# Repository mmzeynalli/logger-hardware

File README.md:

# logger-hardware
This is hardware design for Logger project, built in KiCAD. This project have three UARTs to log any three devices real-time with several options: logging to SD, sending to server (with SIM800), sending data over Bluetooth (to check it from mobile app) and OLED screen.

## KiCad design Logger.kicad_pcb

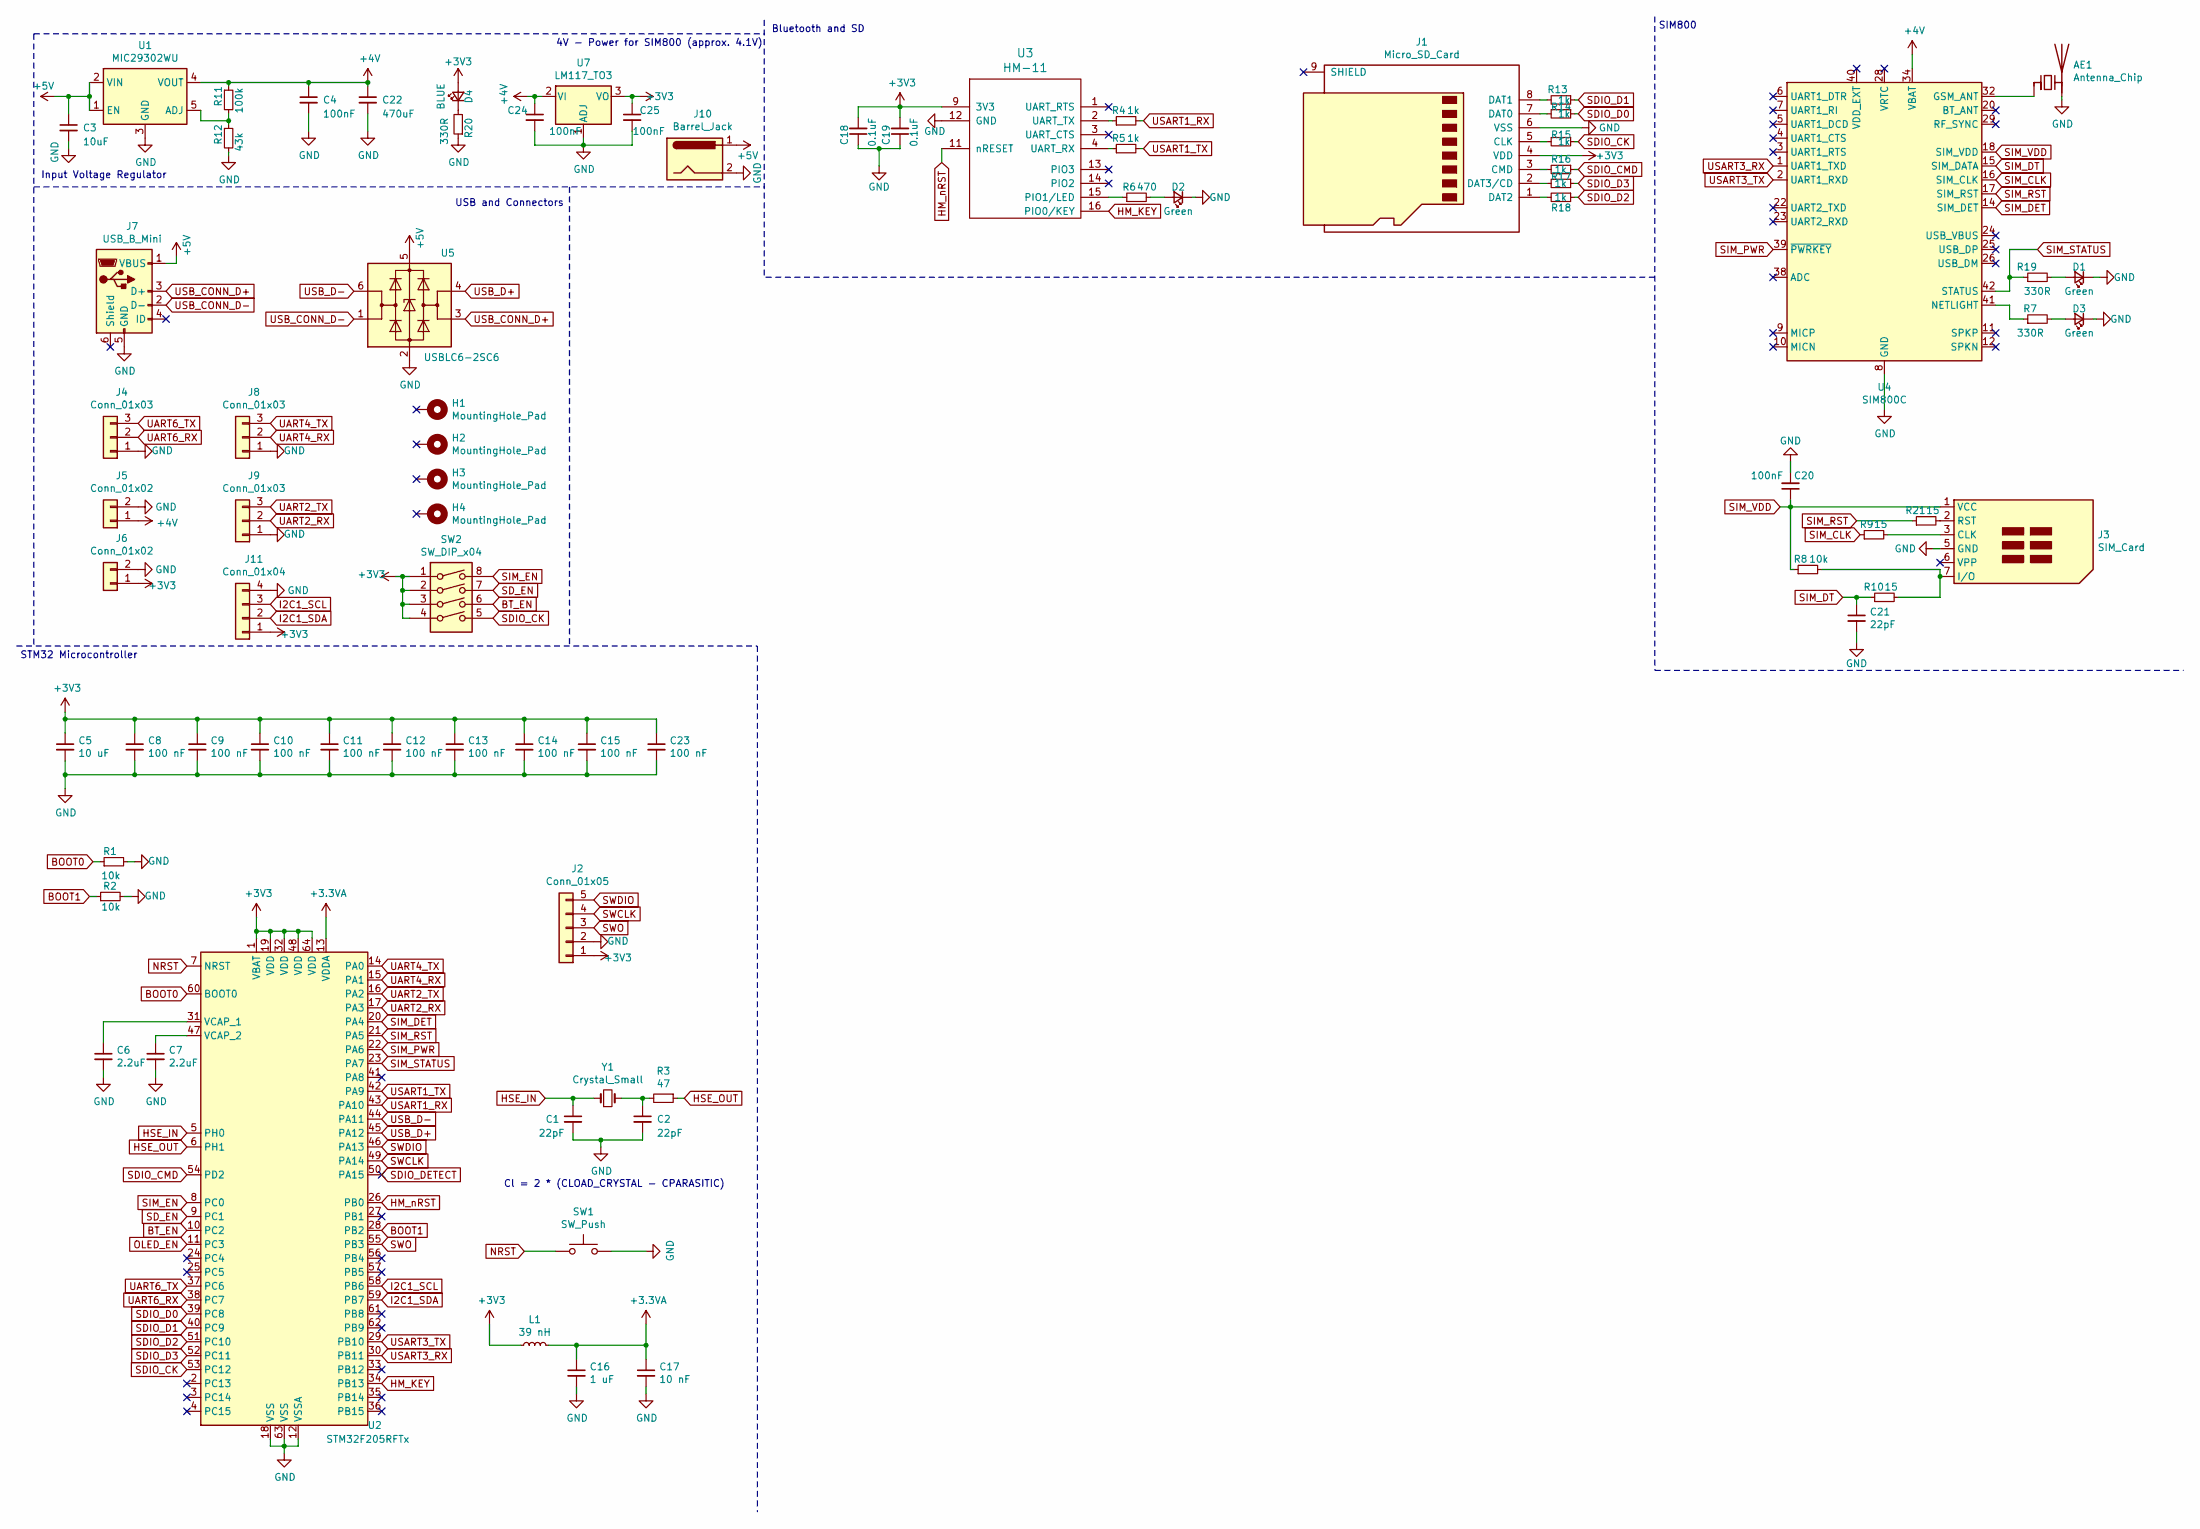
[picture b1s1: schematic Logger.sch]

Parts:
AE1: Antenna_Chip; U.FL_Molex_MCRF_73412-0110_Vertical
C1, C2, C21: 22pF; C_0805_2012Metric
C3: 10uF; C_0805_2012Metric
C4, C20, C24, C25: 100nF; C_0805_2012Metric
C5: 10 uF; C_0805_2012Metric
C6, C7: 2.2uF; C_0805_2012Metric
C8, C9, C10, C11, C12, C13, C14, C15, C23: 100 nF; C_0805_2012Metric
C16: 1 uF; C_0805_2012Metric
C17: 10 nF; C_0805_2012Metric
C18, C19: 0.1uF; C_0805_2012Metric
C22: 470uF; CP_Radial_D8.0mm_P2.50mm
D1, D2, D3: Green; LED_0805_2012Metric
D4: BLUE; LED_1206_3216Metric
H1, H2, H3, H4: MountingHole_Pad; MountingHole_4.3mm_M4_Pad_Via
J1: Micro_SD_Card; microSD_HC_Hirose_DM3D-SF
J2: Conn_01x05; PinHeader_1x05_P2.54mm_Vertical
J3: SIM_Card; microSIM_JAE_SF53S006VCBR2000
J4, J8, J9: Conn_01x03; PinHeader_1x03_P2.54mm_Vertical
J5, J6: Conn_01x02; PinHeader_1x02_P2.54mm_Vertical
J7: USB_B_Mini; USB_Micro-B_Amphenol_10103594-0001LF_Horizontal
J10: Barrel_Jack; BarrelJack_CUI_PJ-063AH_Horizontal
J11: Conn_01x04; PinSocket_1x04_P2.54mm_Vertical
L1: 39 nH; L_Sunlord_MWSA0518_5.4x5.2mm
R1, R2, R8: 10k; R_0805_2012Metric
R3: 47; R_0805_2012Metric
R4, R5, R13, R14, R15, R16, R17, R18: 1k; R_0805_2012Metric
R6: 470; R_0805_2012Metric
R7, R19, R20: 330R; R_0805_2012Metric
R9, R10, R21: 15; R_0805_2012Metric
R11: 100k; R_0805_2012Metric
R12: 43k; R_0805_2012Metric
SW1: SW_Push; SW_Push_1P1T_NO_6x6mm_H9.5mm
SW2: SW_DIP_x04; SW_DIP_SPSTx04_Slide_9.78x12.34mm_W7.62mm_P2.54mm
U1: MIC29302WU; TO-263-5_TabPin3
U2: STM32F205RFTx; LQFP-64_10x10mm_P0.5mm
U3: HM-11
U4: SIM800C; SIMCom_SIM800C
U5: USBLC6-2SC6; SOT-23-6
U7: LM117_TO3; SOT-223-3_TabPin2
Y1: Crystal_Small; Crystal_SMD_HC49-SD

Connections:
+3.3VA: C16.1, C17.1, L1.2, U2.13 (VDDA)
+3V3: C5.1, C8.1, C9.1, C10.1, C11.1, C12.1, C13.1, C14.1, C15.1, C18.2, C19.2, C23.1, C25.1, D4.2 (A), J1.4 (VDD), J2.1, J6.1, J11.1, L1.1, SW2.1, SW2.2, SW2.3, SW2.4, U2.1 (VBAT), U2.19 (VDD), U2.32 (VDD), U2.48 (VDD), U2.64 (VDD), U3.9 (3V3), U7.3 (VO)
+4V: C4.1, C22.1, C24.1, J5.1, R11.1, U1.4 (VOUT), U4.34 (VBAT), U4.35 (VBAT), U7.2 (VI)
+5V: C3.1, J7.1 (VBUS), J10.1, U1.1 (EN), U1.2 (VIN), U5.5 (VBUS)
BOOT0: R1.1, U2.60 (BOOT0)
BOOT1: R2.1, U2.28 (PB2)
BT_EN: SW2.6, U2.10 (PC2)
GND: AE1.2 (PCB_Trace), C1.2, C2.2, C3.2, C4.2, C5.2, C6.2, C7.2, C8.2, C9.2, C10.2, C11.2, C12.2, C13.2, C14.2, C15.2, C16.2, C17.2, C18.1, C19.1, C20.2, C21.2, C22.2, C23.2, C24.2, C25.2, D1.1 (K), D2.1 (K), D3.1 (K), J1.6 (VSS), J2.2, J3.5 (GND), J4.1, J5.2, J6.2, J7.5 (GND), J8.1, J9.1, J10.2, J11.4, R1.2, R2.2, R12.2, R20.1, SW1.2, U1.3 (GND), U2.12 (VSSA), U2.18 (VSS), U2.63 (VSS), U3.12 (GND), U4.8 (GND), U4.13 (GND), U4.19 (GND), U4.21 (GND), U4.27 (GND), U4.30 (GND), U4.31 (GND), U4.33 (GND), U4.36 (GND), U4.37 (GND), U5.2 (GND), U7.1 (ADJ)
HM_KEY: U2.34 (PB13), U3.16 (PIO0/KEY)
HM_nRST: U2.26 (PB0), U3.11 (nRESET)
HSE_IN: C1.1, U2.5 (PH0), Y1.1
HSE_OUT: R3.1, U2.6 (PH1)
I2C1_SCL: J11.3, U2.58 (PB6)
I2C1_SDA: J11.2, U2.59 (PB7)
NRST: SW1.1, U2.7 (NRST)
unnamed: AE1.1 (FEED), U4.32 (GSM_ANT)
unnamed: C2.1, R3.2, Y1.2
unnamed: C6.1, U2.31 (VCAP_1)
unnamed: C7.1, U2.47 (VCAP_2)
unnamed: D1.2 (A), R19.2
unnamed: D2.2 (A), R6.2
unnamed: D3.2 (A), R7.2
unnamed: D4.1 (K), R20.2
unnamed: J1.1 (DAT2), R18.2
unnamed: J1.2 (DAT3/CD), R17.2
unnamed: J1.3 (CMD), R16.2
unnamed: J1.5 (CLK), R15.2
unnamed: J1.7 (DAT0), R14.2
unnamed: J1.8 (DAT1), R13.2
unnamed: J3.2 (RST), R21.2
unnamed: J3.3 (CLK), R9.2
unnamed: J3.7 (I/O), R8.2, R10.2
unnamed: R4.1, U3.2 (UART_TX)
unnamed: R5.1, U3.4 (UART_RX)
unnamed: R6.1, U3.15 (PIO1/LED)
unnamed: R7.1, U4.41 (NETLIGHT)
unnamed: R11.2, R12.1, U1.5 (ADJ)
OLED_EN: U2.11 (PC3)
SDIO_CK: R15.1, SW2.5, U2.53 (PC12)
SDIO_CMD: R16.1, U2.54 (PD2)
SDIO_D0: R14.1, U2.39 (PC8)
SDIO_D1: R13.1, U2.40 (PC9)
SDIO_D2: R18.1, U2.51 (PC10)
SDIO_D3: R17.1, U2.52 (PC11)
SDIO_DETECT: U2.50 (PA15)
SD_EN: SW2.7, U2.9 (PC1)
SIM_CLK: R9.1, U4.16 (SIM_CLK)
SIM_DET: U2.20 (PA4), U4.14 (SIM_DET)
SIM_DT: C21.1, R10.1, U4.15 (SIM_DATA)
SIM_EN: SW2.8, U2.8 (PC0)
SIM_PWR: U2.22 (PA6), U4.39 (~PWRKEY)
SIM_RST: R21.1, U2.21 (PA5), U4.17 (SIM_RST)
SIM_STATUS: R19.1, U2.23 (PA7), U4.42 (STATUS)
SIM_VDD: C20.1, J3.1 (VCC), R8.1, U4.18 (SIM_VDD)
SWCLK: J2.4, U2.49 (PA14)
SWDIO: J2.5, U2.46 (PA13)
SWO: J2.3, U2.55 (PB3)
UART2_RX: J9.2, U2.17 (PA3)
UART2_TX: J9.3, U2.16 (PA2)
UART4_RX: J8.2, U2.15 (PA1)
UART4_TX: J8.3, U2.14 (PA0)
UART6_RX: J4.2, U2.38 (PC7)
UART6_TX: J4.3, U2.37 (PC6)
USART1_RX: R4.2, U2.43 (PA10)
USART1_TX: R5.2, U2.42 (PA9)
USART3_RX: U2.30 (PB11), U4.1 (UART1_TXD)
USART3_TX: U2.29 (PB10), U4.2 (UART1_RXD)
USB_CONN_D+: J7.3 (D+), U5.3 (I/O2)
USB_CONN_D-: J7.2 (D-), U5.1 (I/O1)
USB_D+: U2.45 (PA12), U5.4 (I/O2)
USB_D-: U2.44 (PA11), U5.6 (I/O1)

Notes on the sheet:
Input Voltage Regulator
Cl = 2 * (CLOAD_CRYSTAL - CPARASITIC)
4V - Power for SIM800 (approx. 4.1V)
STM32 Microcontroller
SIM800
USB and Connectors
Bluetooth and SD

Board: 2 copper layers, 76 parts (0 on the bottom side), 69 nets, no tracks yet.

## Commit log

2021-05-29 First commit. Placing is almost finished.
